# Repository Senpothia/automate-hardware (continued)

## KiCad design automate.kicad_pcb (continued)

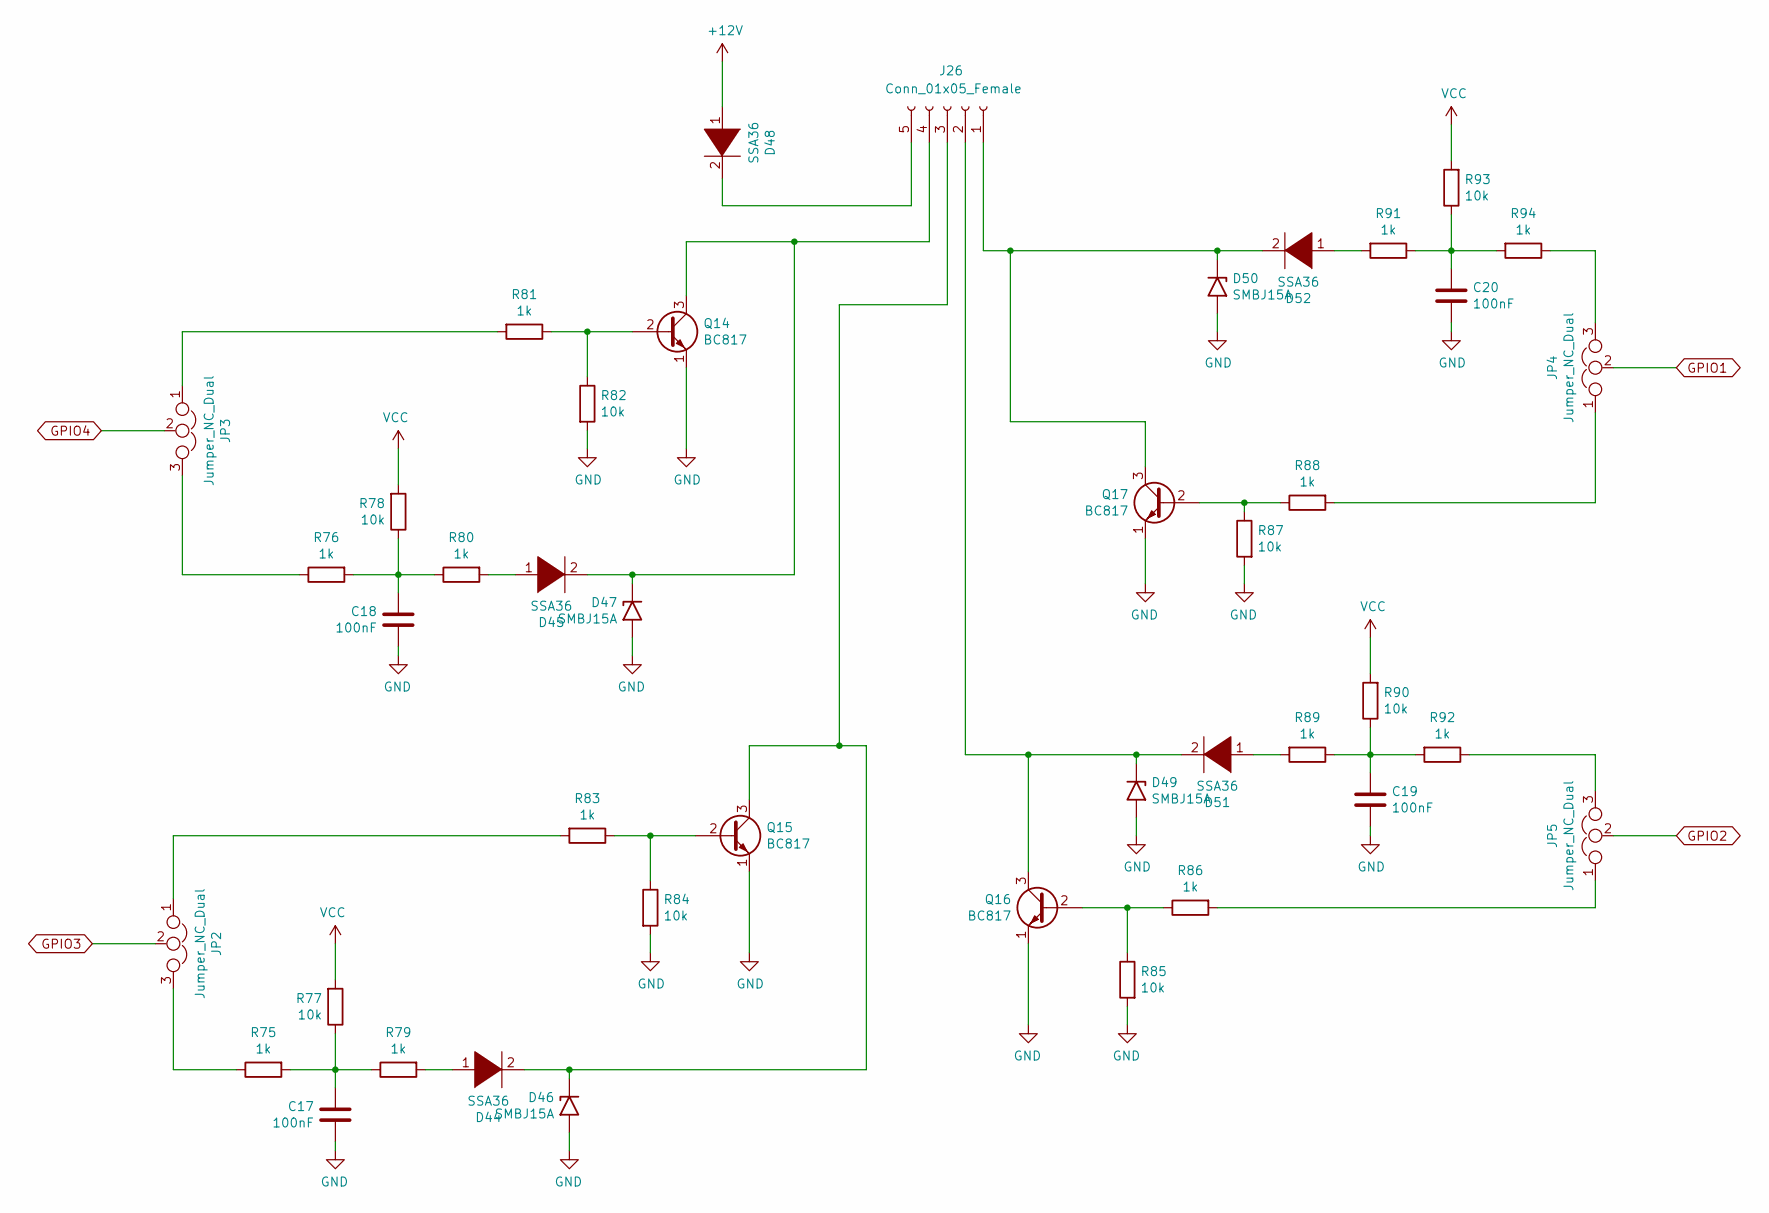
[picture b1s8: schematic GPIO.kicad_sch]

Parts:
C17, C18, C19, C20: 100nF; R_0805_2012Metric_Pad1.20x1.40mm_HandSolder
D44, D45, D48, D51, D52: SSA36; D_SMB_SSA36-Handsoldering
D46, D47, D49, D50: SMBJ15A; D_SMB_Handsoldering
J26: Conn_01x05_Female; conn-5pts-P5mm
JP2, JP3, JP4, JP5: Jumper_NC_Dual; PinHeader_1x03_P2.54mm_Vertical
Q14, Q15, Q16, Q17: BC817; SOT-23.-BC817kicad_mod
R75, R76, R79, R80, R81, R83, R86, R88, R89, R91, R92, R94: 1k; R_0805_2012Metric_Pad1.20x1.40mm_HandSolder
R77, R78, R82, R84, R85, R87, R90, R93: 10k; R_0805_2012Metric_Pad1.20x1.40mm_HandSolder

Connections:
+12V: D48.1 (K); also elsewhere on the board
GND: C17.2, C18.2, C19.2, C20.2, D46.2 (A2), D47.2 (A2), D49.2 (A2), D50.2 (A2), Q14.1 (E), Q15.1 (E), Q16.1 (E), Q17.1 (E), R82.2, R84.2, R85.2, R87.2; also elsewhere on the board
GPIO1: JP4.2; also elsewhere on the board
GPIO2: JP5.2; also elsewhere on the board
GPIO3: JP2.2; also elsewhere on the board
GPIO4: JP3.2; also elsewhere on the board
unnamed: C17.1, R75.2, R77.1, R79.1
unnamed: C18.1, R76.2, R78.1, R80.1
unnamed: C19.1, R89.1, R90.1, R92.2
unnamed: C20.1, R91.1, R93.1, R94.2
unnamed: D44.1 (K), R79.2
unnamed: D44.2 (A), D46.1 (A1), J26.3, Q15.3 (C)
unnamed: D45.1 (K), R80.2
unnamed: D45.2 (A), D47.1 (A1), J26.4, Q14.3 (C)
unnamed: D48.2 (A), J26.5
unnamed: D49.1 (A1), D51.2 (A), J26.2, Q16.3 (C)
unnamed: D50.1 (A1), D52.2 (A), J26.1, Q17.3 (C)
unnamed: D51.1 (K), R89.2
unnamed: D52.1 (K), R91.2
unnamed: JP2.1, R83.2
unnamed: JP2.3, R75.1
unnamed: JP3.1, R81.2
unnamed: JP3.3, R76.1
unnamed: JP4.1, R88.2
unnamed: JP4.3, R94.1
unnamed: JP5.1, R86.2
unnamed: JP5.3, R92.1
unnamed: Q14.2 (B), R81.1, R82.1
unnamed: Q15.2 (B), R83.1, R84.1
unnamed: Q16.2 (B), R85.1, R86.1
unnamed: Q17.2 (B), R87.1, R88.1
VCC: R77.2, R78.2, R90.2, R93.2; also elsewhere on the board

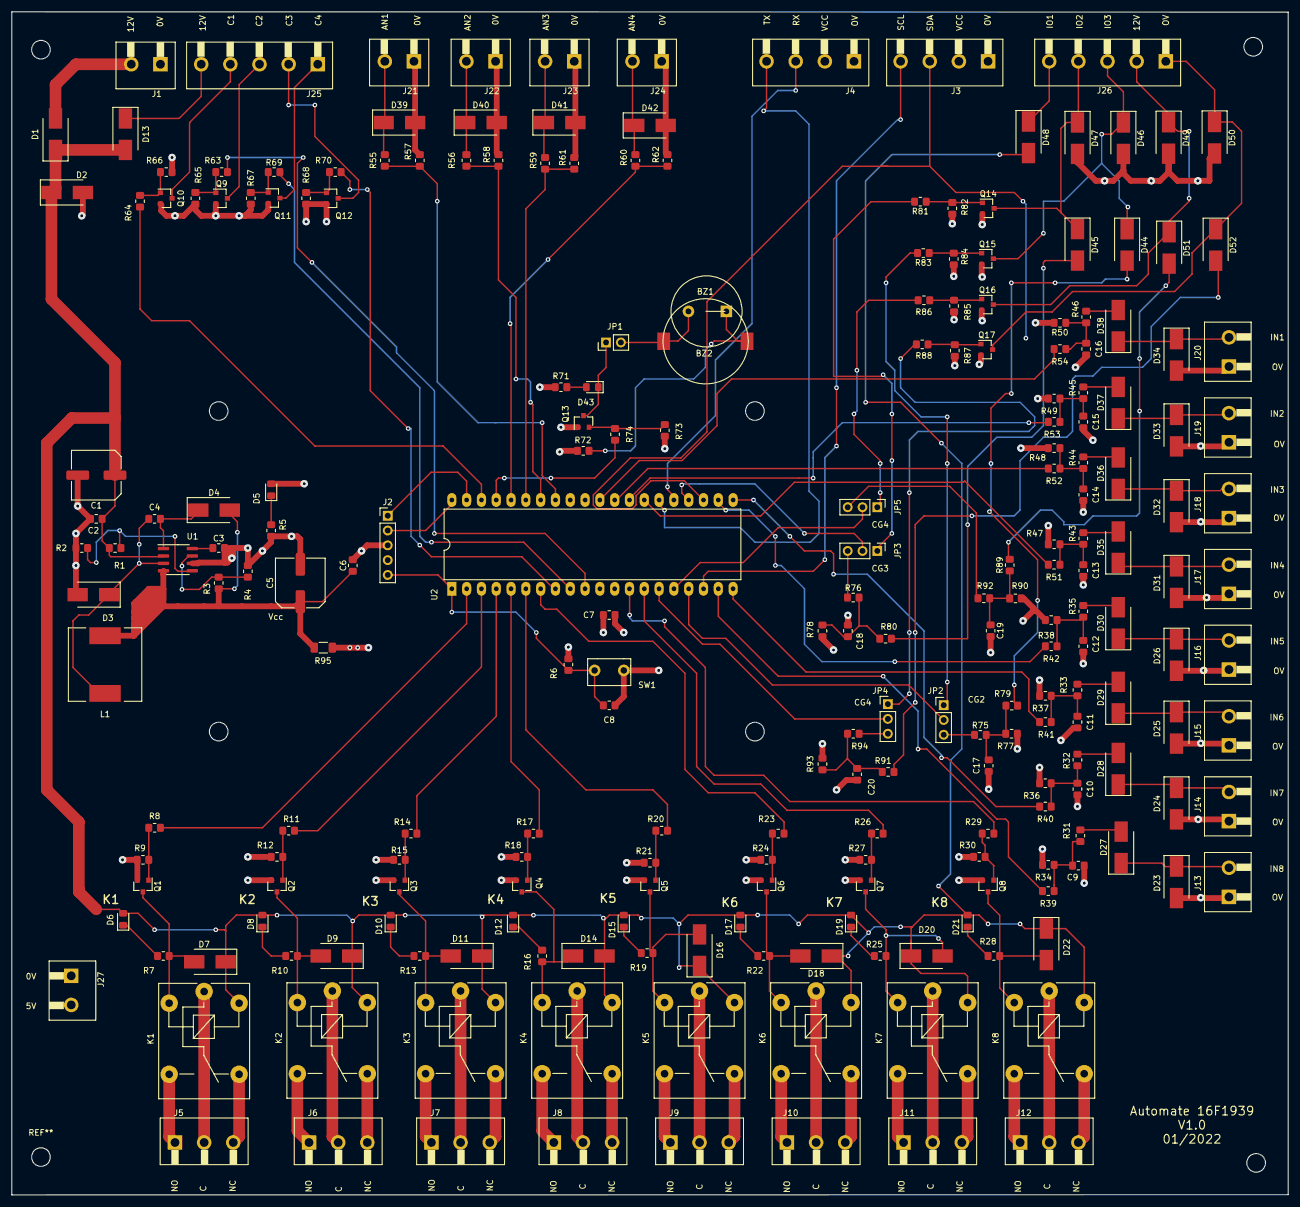
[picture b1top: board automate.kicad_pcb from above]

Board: 4 copper layers, 219.0 x 203.0 mm, 230 parts (0 on the bottom side), 162 nets.

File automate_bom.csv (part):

Source:,C:\Users\Michel\Documents\Projets-kicad\automate\automate.sch,,,,,,,
Date:,22/01/2022 15:14:08,,,,,,,
Tool:,Eeschema (6.0.0),,,,,,,
Generator:,C:\Program Files\KiCad\6.0\bin\scripting\plugins/bom_csv_grouped_by_value.py,,,,,,,
Component Count:,230,,,,,,,
,,,,,,,,
Individual Components:,,,,,,,,
,,,,,,,,
Item,Qty,Reference(s),Value,LibPart,Footprint,Datasheet,MANUFACTURER_PART_NUMBER,VENDOR
,,BZ1,Buzzer,Device:Buzzer,buzzer_perso:Buzzer_Mallory_AST1109MLTRQ,~,,
,,BZ2,Buzzer,Device:Buzzer,buzzer_perso:Buzzer_12x9.5RM7.6,~,,
,,C1,100µF,Device:CP,capacitor_perso:C_Elec_8x6.2,,,
,,C2,100nF,Device:C,Resistor_SMD:R_0805_2012Metric_Pad1.20x1.40mm_HandSolder,~,,
,,C3,2.2nF,Device:C,Resistor_SMD:R_0805_2012Metric_Pad1.20x1.40mm_HandSolder,~,,
,,C4,100nF,Device:C,Resistor_SMD:R_0805_2012Metric_Pad1.20x1.40mm_HandSolder,~,,
,,C5,100µF,Device:CP,capacitor_perso:C_Elec_8x6.2,,,
,,C6,100nF,Device:C,Resistor_SMD:R_0805_2012Metric_Pad1.20x1.40mm_HandSolder,~,,
,,C7,100nF,Device:C,Resistor_SMD:R_0805_2012Metric_Pad1.20x1.40mm_HandSolder,~,,
,,C8,100nF,Device:C,Resistor_SMD:R_0805_2012Metric_Pad1.20x1.40mm_HandSolder,~,,
,,C9,100nF,Device:C,Resistor_SMD:R_0805_2012Metric_Pad1.20x1.40mm_HandSolder,~,,
,,C10,100nF,Device:C,Resistor_SMD:R_0805_2012Metric_Pad1.20x1.40mm_HandSolder,~,,
,,C11,100nF,Device:C,Resistor_SMD:R_0805_2012Metric_Pad1.20x1.40mm_HandSolder,~,,
,,C12,100nF,Device:C,Resistor_SMD:R_0805_2012Metric_Pad1.20x1.40mm_HandSolder,~,,
,,C13,100nF,Device:C,Resistor_SMD:R_0805_2012Metric_Pad1.20x1.40mm_HandSolder,~,,
,,C14,100nF,Device:C,Resistor_SMD:R_0805_2012Metric_Pad1.20x1.40mm_HandSolder,~,,
,,C15,100nF,Device:C,Resistor_SMD:R_0805_2012Metric_Pad1.20x1.40mm_HandSolder,~,,
,,C16,100nF,Device:C,Resistor_SMD:R_0805_2012Metric_Pad1.20x1.40mm_HandSolder,~,,
,,C17,100nF,Device:C,Resistor_SMD:R_0805_2012Metric_Pad1.20x1.40mm_HandSolder,~,,
,,C18,100nF,Device:C,Resistor_SMD:R_0805_2012Metric_Pad1.20x1.40mm_HandSolder,~,,
,,C19,100nF,Device:C,Resistor_SMD:R_0805_2012Metric_Pad1.20x1.40mm_HandSolder,~,,
,,C20,100nF,Device:C,Resistor_SMD:R_0805_2012Metric_Pad1.20x1.40mm_HandSolder,~,,
,,D1,SSA36,pspice:DIODE,diodes_perso:D_SMB_SSA36-Handsoldering,~,,
,,D2,SMBJ15A,Diode:SM6T15A,Diode_SMD:D_SMB_Handsoldering,https://www.st.com/resource/en/datasheet/sm6t.pdf,,
,,D3,DIODE,pspice:DIODE,diodes_perso:D_SMB_SSA36-Handsoldering,~,,
,,D4,SSA36,pspice:DIODE,diodes_perso:D_SMB_SSA36-Handsoldering,~,,
,,D5,LED,Device:LED,Diode_SMD:D_0805_2012Metric_Pad1.15x1.40mm_HandSolder,~,,
,,D6,LED,Device:LED,Diode_SMD:D_0805_2012Metric_Pad1.15x1.40mm_HandSolder,~,,
,,D7,SSA36,pspice:DIODE,diodes_perso:D_SMB_SSA36-Handsoldering,~,,
,,D8,LED,Device:LED,Diode_SMD:D_0805_2012Metric_Pad1.15x1.40mm_HandSolder,~,,
,,D9,SSA36,pspice:DIODE,diodes_perso:D_SMB_SSA36-Handsoldering,~,,
,,D10,LED,Device:LED,Diode_SMD:D_0805_2012Metric_Pad1.15x1.40mm_HandSolder,~,,
,,D11,SSA36,pspice:DIODE,diodes_perso:D_SMB_SSA36-Handsoldering,~,,
,,D12,LED,Device:LED,Diode_SMD:D_0805_2012Metric_Pad1.15x1.40mm_HandSolder,~,,
,,D13,SSA36,pspice:DIODE,diodes_perso:D_SMB_SSA36-Handsoldering,~,,
,,D14,SSA36,pspice:DIODE,Diode_SMD:D_SMB_Handsoldering,~,,
,,D15,LED,Device:LED,Diode_SMD:D_0805_2012Metric_Pad1.15x1.40mm_HandSolder,~,,
,,D16,SSA36,pspice:DIODE,diodes_perso:D_SMB_SSA36-Handsoldering,~,,
,,D17,LED,Device:LED,Diode_SMD:D_0805_2012Metric_Pad1.15x1.40mm_HandSolder,~,,
,,D18,SSA36,pspice:DIODE,diodes_perso:D_SMB_SSA36-Handsoldering,~,,
,,D19,LED,Device:LED,Diode_SMD:D_0805_2012Metric_Pad1.15x1.40mm_HandSolder,~,,
,,D20,SSA36,pspice:DIODE,diodes_perso:D_SMB_SSA36-Handsoldering,~,,
,,D21,LED,Device:LED,Diode_SMD:D_0805_2012Metric_Pad1.15x1.40mm_HandSolder,~,,
,,D22,DIODE,pspice:DIODE,diodes_perso:D_SMB_SSA36-Handsoldering,~,,
,,D23,SMBJ15A,Diode:SM6T15A,Diode_SMD:D_SMB_Handsoldering,https://www.st.com/resource/en/datasheet/sm6t.pdf,,
,,D24,SMBJ15A,Diode:SM6T15A,Diode_SMD:D_SMB_Handsoldering,https://www.st.com/resource/en/datasheet/sm6t.pdf,,
,,D25,SMBJ15A,Diode:SM6T15A,Diode_SMD:D_SMB_Handsoldering,https://www.st.com/resource/en/datasheet/sm6t.pdf,,
,,D26,SMBJ15A,Diode:SM6T15A,Diode_SMD:D_SMB_Handsoldering,https://www.st.com/resource/en/datasheet/sm6t.pdf,,
,,D27,SSA36,pspice:DIODE,diodes_perso:D_SMB_SSA36-Handsoldering,~,,
,,D28,SSA36,pspice:DIODE,diodes_perso:D_SMB_SSA36-Handsoldering,~,,
,,D29,SSA36,pspice:DIODE,diodes_perso:D_SMB_SSA36-Handsoldering,~,,
,,D30,SSA36,pspice:DIODE,diodes_perso:D_SMB_SSA36-Handsoldering,~,,
,,D31,SMBJ15A,Diode:SM6T15A,Diode_SMD:D_SMB_Handsoldering,https://www.st.com/resource/en/datasheet/sm6t.pdf,,
,,D32,SMBJ15A,Diode:SM6T15A,Diode_SMD:D_SMB_Handsoldering,https://www.st.com/resource/en/datasheet/sm6t.pdf,,
,,D33,SMBJ15A,Diode:SM6T15A,Diode_SMD:D_SMB_Handsoldering,https://www.st.com/resource/en/datasheet/sm6t.pdf,,
,,D34,SMBJ15A,Diode:SM6T15A,Diode_SMD:D_SMB_Handsoldering,https://www.st.com/resource/en/datasheet/sm6t.pdf,,
,,D35,SSA36,pspice:DIODE,diodes_perso:D_SMB_SSA36-Handsoldering,~,,
,,D36,SSA36,pspice:DIODE,diodes_perso:D_SMB_SSA36-Handsoldering,~,,
,,D37,SSA36,pspice:DIODE,diodes_perso:D_SMB_SSA36-Handsoldering,~,,
,,D38,SSA36,pspice:DIODE,diodes_perso:D_SMB_SSA36-Handsoldering,~,,
,,D39,SMBJ15A,Diode:SM6T15A,Diode_SMD:D_SMB_Handsoldering,https://www.st.com/resource/en/datasheet/sm6t.pdf,,
,,D40,SMBJ15A,Diode:SM6T15A,Diode_SMD:D_SMB_Handsoldering,https://www.st.com/resource/en/datasheet/sm6t.pdf,,
,,D41,SMBJ15A,Diode:SM6T15A,Diode_SMD:D_SMB_Handsoldering,https://www.st.com/resource/en/datasheet/sm6t.pdf,,
,,D42,SMBJ15A,Diode:SM6T15A,Diode_SMD:D_SMB_Handsoldering,https://www.st.com/resource/en/datasheet/sm6t.pdf,,
,,D43,LED,Device:LED,LED_SMD:LED_0805_2012Metric_Pad1.15x1.40mm_HandSolder,~,,
,,D44,SSA36,pspice:DIODE,diodes_perso:D_SMB_SSA36-Handsoldering,~,,
,,D45,SSA36,pspice:DIODE,diodes_perso:D_SMB_SSA36-Handsoldering,~,,
,,D46,SMBJ15A,Diode:SM6T15A,Diode_SMD:D_SMB_Handsoldering,https://www.st.com/resource/en/datasheet/sm6t.pdf,,
,,D47,SMBJ15A,Diode:SM6T15A,Diode_SMD:D_SMB_Handsoldering,https://www.st.com/resource/en/datasheet/sm6t.pdf,,
,,D48,SSA36,pspice:DIODE,diodes_perso:D_SMB_SSA36-Handsoldering,~,,
,,D49,SMBJ15A,Diode:SM6T15A,Diode_SMD:D_SMB_Handsoldering,https://www.st.com/resource/en/datasheet/sm6t.pdf,,
,,D50,SMBJ15A,Diode:SM6T15A,Diode_SMD:D_SMB_Handsoldering,https://www.st.com/resource/en/datasheet/sm6t.pdf,,
,,D51,SSA36,pspice:DIODE,diodes_perso:D_SMB_SSA36-Handsoldering,~,,
,,D52,SSA36,pspice:DIODE,diodes_perso:D_SMB_SSA36-Handsoldering,~,,
,,J1,Conn_01x02_Female,Connector:Conn_01x02_Female,connectors:conn-2pts-P5mm,~,,
,,J2,Conn_01x05_Female,Connector:Conn_01x05_Female,Connector_PinHeader_2.54mm:PinHeader_1x05_P2.54mm_Vertical,~,,
,,J3,Conn_01x04_Female,Connector:Conn_01x04_Female,connectors:conn-4pts-P5mm,~,,
,,J4,Conn_01x04_Female,Connector:Conn_01x04_Female,connectors:conn-4pts-P5mm,~,,
,,J5,Conn_01x03_Female,Connector:Conn_01x03_Female,connectors:conn-3pts-P5mm,~,,
,,J6,Conn_01x03_Female,Connector:Conn_01x03_Female,connectors:conn-3pts-P5mm,~,,
,,J7,Conn_01x03_Female,Connector:Conn_01x03_Female,connectors:conn-3pts-P5mm,~,,
,,J8,Conn_01x03_Female,Connector:Conn_01x03_Female,connectors:conn-3pts-P5mm,~,,
,,J9,Conn_01x03_Female,Connector:Conn_01x03_Female,connectors:conn-3pts-P5mm,~,,
,,J10,Conn_01x03_Female,Connector:Conn_01x03_Female,connectors:conn-3pts-P5mm,~,,
,,J11,Conn_01x03_Female,Connector:Conn_01x03_Female,connectors:conn-3pts-P5mm,~,,
,,J12,Conn_01x03_Female,Connector:Conn_01x03_Female,connectors:conn-3pts-P5mm,~,,
,,J13,Conn_01x02_Female,Connector:Conn_01x02_Female,connectors:conn-2pts-P5mm,~,,
,,J14,Conn_01x02_Female,Connector:Conn_01x02_Female,connectors:conn-2pts-P5mm,~,,
,,J15,Conn_01x02_Female,Connector:Conn_01x02_Female,connectors:conn-2pts-P5mm,~,,
,,J16,Conn_01x02_Female,Connector:Conn_01x02_Female,connectors:conn-2pts-P5mm,~,,
,,J17,Conn_01x02_Female,Connector:Conn_01x02_Female,connectors:conn-2pts-P5mm,~,,
,,J18,Conn_01x02_Female,Connector:Conn_01x02_Female,connectors:conn-2pts-P5mm,~,,
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
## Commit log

2022-02-25 version 1
